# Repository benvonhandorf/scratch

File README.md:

# scratch

This repo exists as a disorganized place for me to drop code which I may or may not care about.  Assume everything here has no value.

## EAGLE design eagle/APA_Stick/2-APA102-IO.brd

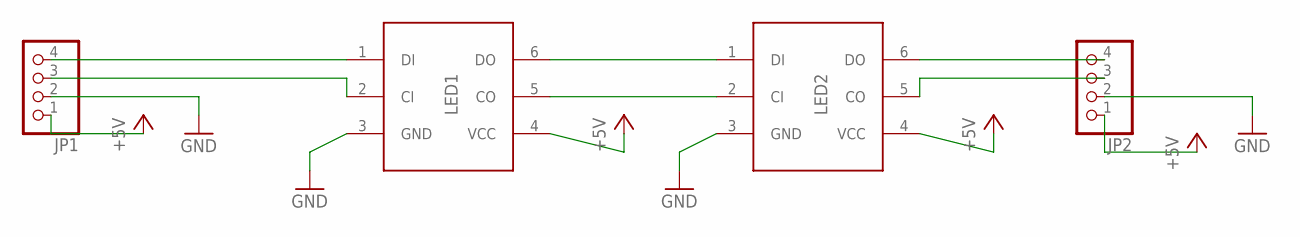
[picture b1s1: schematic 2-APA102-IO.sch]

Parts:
JP1, JP2: PINHD-1X4; 1X04
LED1, LED2: APA1025050

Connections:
+5V: JP1.1, JP2.1, LED1.4 (VCC), LED2.4 (VCC)
GND: JP1.2, JP2.2, LED1.3 (GND), LED2.3 (GND)
unnamed: JP1.4, LED1.1 (DI)
unnamed: JP1.3, LED1.2 (CI)
unnamed: LED1.6 (DO), LED2.1 (DI)
unnamed: LED1.5 (CO), LED2.2 (CI)
unnamed: JP2.3, LED2.5 (CO)
unnamed: JP2.4, LED2.6 (DO)

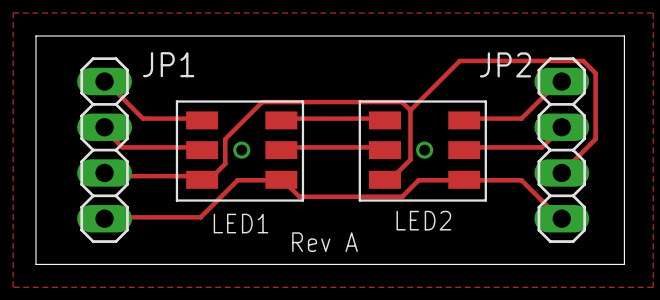
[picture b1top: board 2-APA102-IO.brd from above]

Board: 2 copper layers, 32.7 x 12.7 mm, 4 parts (0 on the bottom side), 8 nets.

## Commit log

2018-03-05 Moved esp32 hello_world project into scratch
2018-03-23 Organization
2018-03-23 Another test board
2019-05-04 catchup
2019-05-07 2019 May PCB 1
2019-05-19 WSPR Query and processing
2019-06-26 Initial work on sota qsl card
2019-06-26 static map work
2019-07-06 CW work
2019-07-06 CW Synthesis starting to work
2019-07-07 Timing issues worked out
2019-07-07 fix gitignore
2019-07-07 Usable
2019-07-08 Add polly caching and koch file generation
2019-07-08 Improvements
2019-07-10 Refactor and ability to suppress TTS
2019-07-10 Sota API start
2019-07-11 Reference card construction basics
2019-07-16 Fixes
2019-07-28 Fix bug
2019-08-15 GPX file construction
2019-08-24 Added support for CWOps lessons
2019-08-27 Work on improving sota reference card
2019-08-29 Added speed support
2019-09-27 Scripted
2019-10-20 ADIF CQRLog to POTA log converter - First attempt
2020-01-17 Added hexboard sketch
2020-05-16 PSP Joystick Breakout work
2020-05-17 PSP joystick prototype order
2020-05-29 FPC Breakout Work
2020-06-20 FPC Breakout
2020-06-21 Initial work on ESP8266 BMP board
2020-06-21 ESP8266 BMP design v1
2020-06-23 PAW3204 Breakout WIP
2020-06-24 Moved PAW3204 board to SCR
2020-07-21 Cleanup
2020-08-11 Add gpx
2020-12-30 WIP Macro Keyboard
2020-12-31 Macro keyboard WIP
2021-03-07 Breakout Test Boards 2021-03
